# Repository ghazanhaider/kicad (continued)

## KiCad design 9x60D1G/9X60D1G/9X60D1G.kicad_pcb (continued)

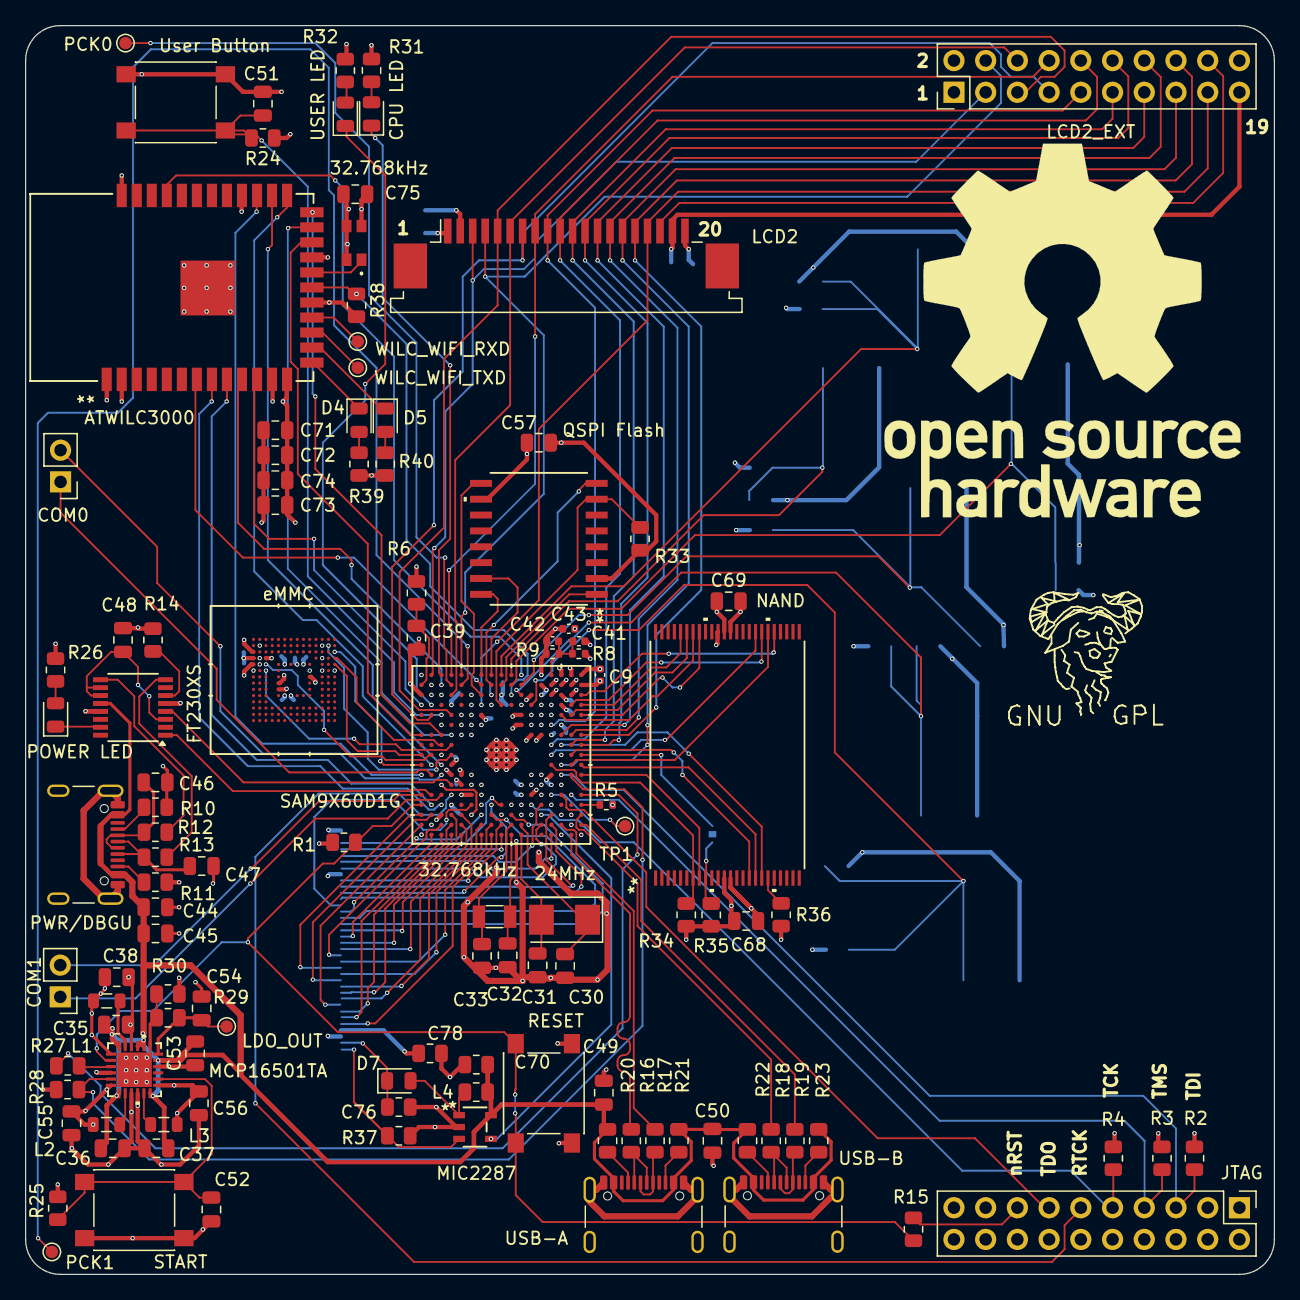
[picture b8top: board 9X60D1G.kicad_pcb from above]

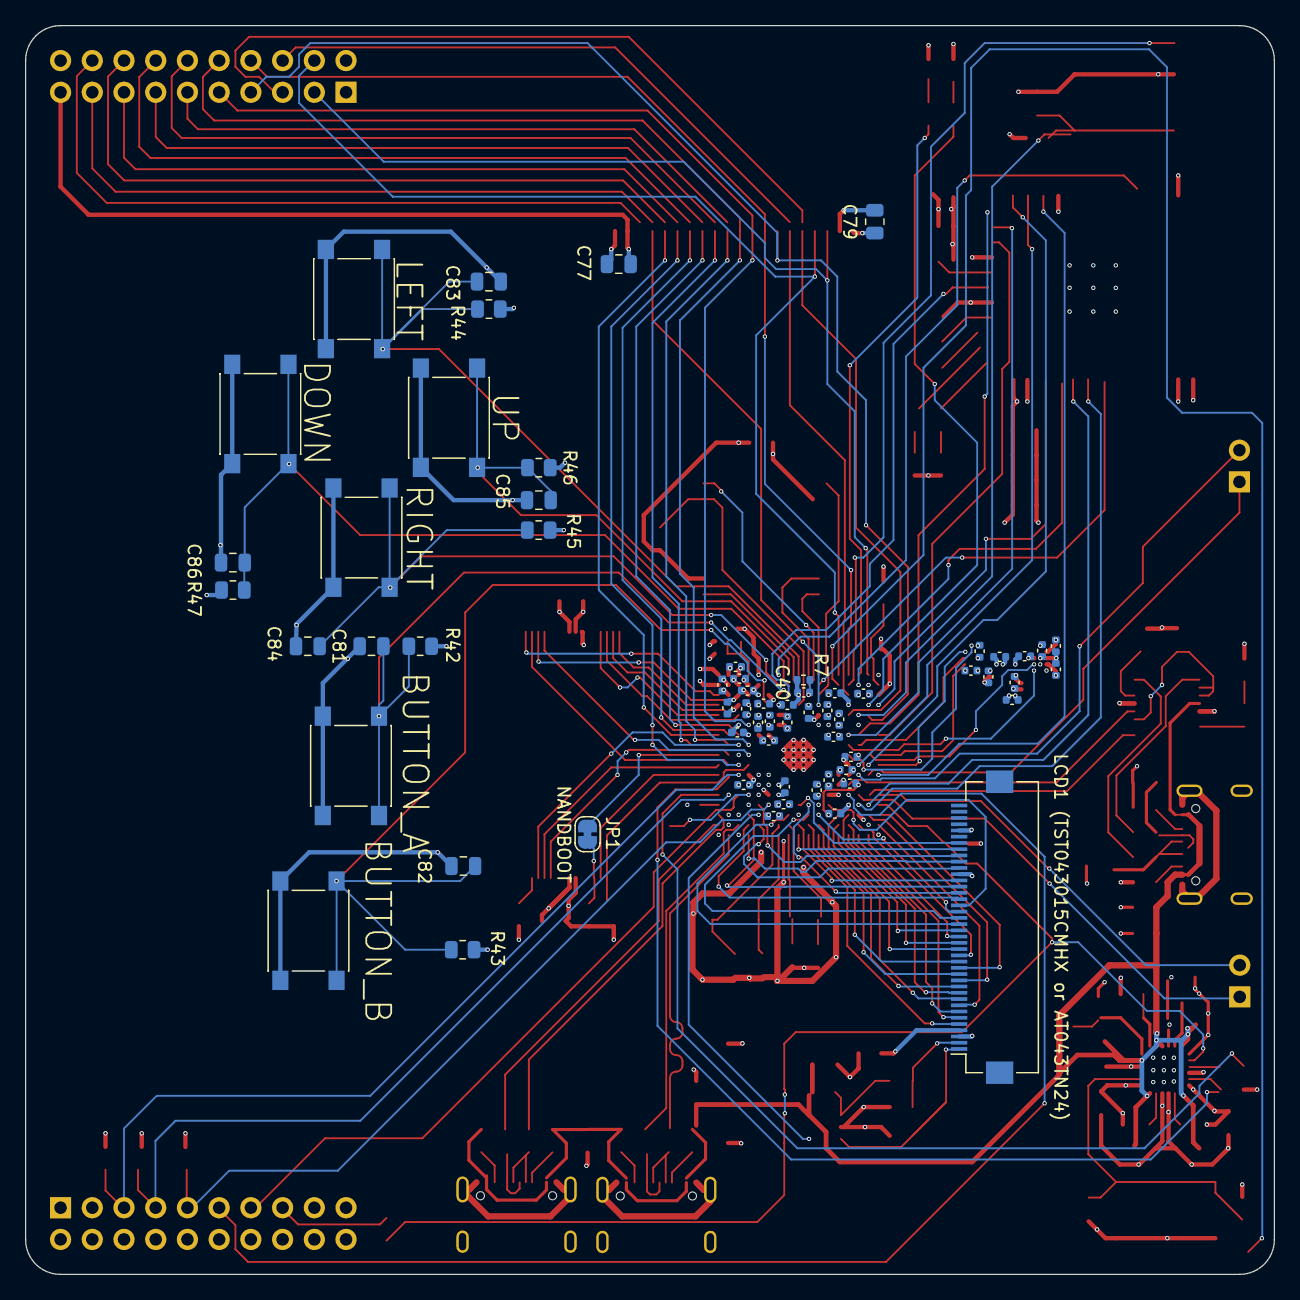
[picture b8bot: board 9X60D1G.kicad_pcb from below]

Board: 4 copper layers, 100.0 x 100.0 mm, 179 parts (63 on the bottom side), 168 nets.

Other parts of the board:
footprintone: OSHW-Logo_28.5x30mm_SilkScreen
footprinttwo: Symbol_GNU-Logo_SilkscreenTop

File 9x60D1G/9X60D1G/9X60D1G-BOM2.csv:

"Reference","Value","Datasheet","Footprint","Qty","DNP"
"C1,C2,C3,C4,C5,C6,C7,C8,C9,C10,C11,C12,C13,C14,C15,C16,C17,C18,C19,C20,C21,C22,C23,C24,C25,C26,C27,C28,C29,C34,C39,C41,C42,C44,C48,C51,C52,C57,C68,C69,C71,C72,C75,C81,C82,C83,C84,C85,C86","100nF","~","-- mixed values --","49",""
"C30,C31","27pF","~","Capacitor_SMD:C_0805_2012Metric","2",""
"C32,C33","18pF","~","Capacitor_SMD:C_0805_2012Metric","2",""
"C35,C36,C37,C43,C53,C54,C77,C78","4.7uF","~","-- mixed values --","8",""
"C38,C55,C56","22uF","~","Capacitor_SMD:C_0805_2012Metric","3",""
"C40","22pF","~","Capacitor_SMD:C_0402_1005Metric","1",""
"C45,C49,C50,C73","47uF","~","Capacitor_SMD:C_0805_2012Metric","4",""
"C46,C47","47pF","~","Capacitor_SMD:C_0805_2012Metric","2",""
"C58,C59,C60,C61,C62,C63,C64,C65,C66,C67,C74","2.2uF","~","-- mixed values --","11",""
"C70,C76,C79","1uF","~","Resistor_SMD:R_0805_2012Metric","3",""
"D1","PWR_LED","~","LED_SMD:LED_0805_2012Metric","1",""
"D2","CPU_LED","~","LED_SMD:LED_0805_2012Metric","1",""
"D3","USER_LED","~","LED_SMD:LED_0805_2012Metric","1",""
"D4","WILC_LED_GREEN","~","LED_SMD:LED_0805_2012Metric","1",""
"D5","WILC_LED_RED","~","LED_SMD:LED_0805_2012Metric","1",""
"D7","D_Schottky","~","Diode_SMD:D_0805_2012Metric","1",""
"J1","JTAG","~","Connector_PinHeader_2.54mm:PinHeader_2x10_P2.54mm_Vertical","1",""
"J2","LCD1","~","Connector_FFC-FPC:Hirose_FH12-40S-0.5SH_1x40-1MP_P0.50mm_Horizontal","1",""
"J3,J4,J5","USB4105-GF-A","USB4105-GF-A","Connector_USB:USB_C_Receptacle_GCT_USB4105-xx-A_16P_TopMnt_Horizontal","3",""
"J6","FLEXCOM0","~","Connector_PinHeader_2.54mm:PinHeader_1x02_P2.54mm_Vertical","1",""
"J7","FLEXCOM1","~","Connector_PinHeader_2.54mm:PinHeader_1x02_P2.54mm_Vertical","1",""
"J8","LCD2","~","Connector_FFC-FPC:TE_2-84952-0_1x20-1MP_P1.0mm_Horizontal","1",""
"J9","LCD2_EXT","~","Connector_PinHeader_2.54mm:PinHeader_2x10_P2.54mm_Vertical","1",""
"JP1","NANDBOOT","~","Jumper:SolderJumper-2_P1.3mm_Bridged_RoundedPad1.0x1.5mm","1",""
"L1,L2,L3","1.5uH","~","Inductor_SMD:L_0805_2012Metric","3",""
"L4","15uH","~","Resistor_SMD:R_0805_2012Metric","1",""
"R1,R6,R28,R33","10K","~","Resistor_SMD:R_0805_2012Metric","4",""
"R2,R3,R4,R14,R24,R25,R34,R35,R36,R38,R42,R43,R44,R45,R46,R47","100K","~","Resistor_SMD:R_0805_2012Metric","16",""
"R5","5K62 1%","~","Resistor_SMD:R_0402_1005Metric","1",""
"R7","20K 1%","~","Resistor_SMD:R_0402_1005Metric","1",""
"R8,R9","4K7 1%","~","Resistor_SMD:R_0402_1005Metric","2",""
"R10,R11","5.1K 1%","~","Resistor_SMD:R_0805_2012Metric","2",""
"R12,R13,R16,R17,R18,R19","27","~","Resistor_SMD:R_0805_2012Metric","6",""
"R15","100","~","Resistor_SMD:R_0805_2012Metric","1",""
"R20,R21,R22,R23","56K","~","Resistor_SMD:R_0805_2012Metric","4",""
"R26,R31,R32","750","~","Resistor_SMD:R_0805_2012Metric","3",""
"R27,R39,R40","1K","~","Resistor_SMD:R_0805_2012Metric","3",""
"R29","270K 1%","~","Resistor_SMD:R_0805_2012Metric","1",""
"R30","100K 1%","~","Resistor_SMD:R_0805_2012Metric","1",""
"R37","6.3","~","Resistor_SMD:R_0805_2012Metric","1",""
"SW1","RESET","~","Button_Switch_SMD:SW_Push_1P1T_NO_6x6mm_H9.5mm","1",""
"SW2","BUTTON","~","Button_Switch_SMD:SW_Push_1P1T_NO_6x6mm_H9.5mm","1",""
"SW3","START","~","Button_Switch_SMD:SW_Push_1P1T_NO_6x6mm_H9.5mm","1",""
"SW4","BUTTON_A","~","Button_Switch_SMD:SW_Push_1P1T_NO_6x6mm_H9.5mm","1",""
"SW5","BUTTON_B","~","Button_Switch_SMD:SW_Push_1P1T_NO_6x6mm_H9.5mm","1",""
"SW6","BUTTON_LEFT","~","Button_Switch_SMD:SW_Push_1P1T_NO_6x6mm_H9.5mm","1",""
"SW7","BUTTON_RIGHT","~","Button_Switch_SMD:SW_Push_1P1T_NO_6x6mm_H9.5mm","1",""
"SW8","BUTTON_UP","~","Button_Switch_SMD:SW_Push_1P1T_NO_6x6mm_H9.5mm","1",""
"SW9","BUTTON_DOWN","~","Button_Switch_SMD:SW_Push_1P1T_NO_6x6mm_H9.5mm","1",""
"TP1","JTAGSEL","~","TestPoint:TestPoint_Pad_D1.0mm","1",""
"TP2","LDO_OUT","~","TestPoint:TestPoint_Pad_D1.0mm","1",""
"TP3","WILC_WIFI_TXD","~","TestPoint:TestPoint_Pad_D1.0mm","1",""
"TP4","WILC_WIFI_RXD","~","TestPoint:TestPoint_Pad_D1.0mm","1",""
"TP5","PCK1","~","TestPoint:TestPoint_Pad_D1.0mm","1",""
"TP6","PCK0","~","TestPoint:TestPoint_Pad_D1.0mm","1",""
"U2","SAM9X60D1G-I/4FB","SAM9X60D1G-I/4FB","GhazanCustom:233TFBGA_MCH","1",""
"U3","MCP16501TA-E/RMB","MCP16501TA-E/RMB","GhazanCustom:VQFN24_RMB_MCH","1",""
"U4","FT230XS","FT230XS-U","Package_SO:SSOP-16_3.9x4.9mm_P0.635mm","1",""
"U5","S25FL256SDPMFV001","S25FL256SDPMFV001","GhazanCustom:SO3016_SPA","1",""
"U6","THGBMTG5D1LBAIL","THGBMTG5D1LBAIL","GhazanCustom:BGA153_THGBMJ_KIO","1",""
"U7","MT29F4G08ABAFAWP-IT:F","MT29F4G08ABAFAWP-IT:F","GhazanCustom:TSOPI-48_MRN","1",""
"U8","MIC2287CYD5-TR","MIC2287CYD5-TR","GhazanCustom:TSOT-23-5_D5_MCH","1",""
"U9","ATWILC3000-MR110CA","ATWILC3000-MR110CA","GhazanCustom:ATWILC3000-MR110CA_MCH","1",""
"Y1","32.768kHz","~","Crystal:Crystal_SMD_3215-2Pin_3.2x1.5mm","1",""
"Y2","24MHz","~","Crystal:Crystal_SMD_5032-2Pin_5.0x3.2mm","1",""
"Y3","ASH7KW-32.768KHZ-L-T","https://abracon.com/Oscillators/ASH7KW.pdf","ASH7KW32768kHzLT","1",""

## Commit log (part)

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2024-02-10 second
2024-02-10 third
